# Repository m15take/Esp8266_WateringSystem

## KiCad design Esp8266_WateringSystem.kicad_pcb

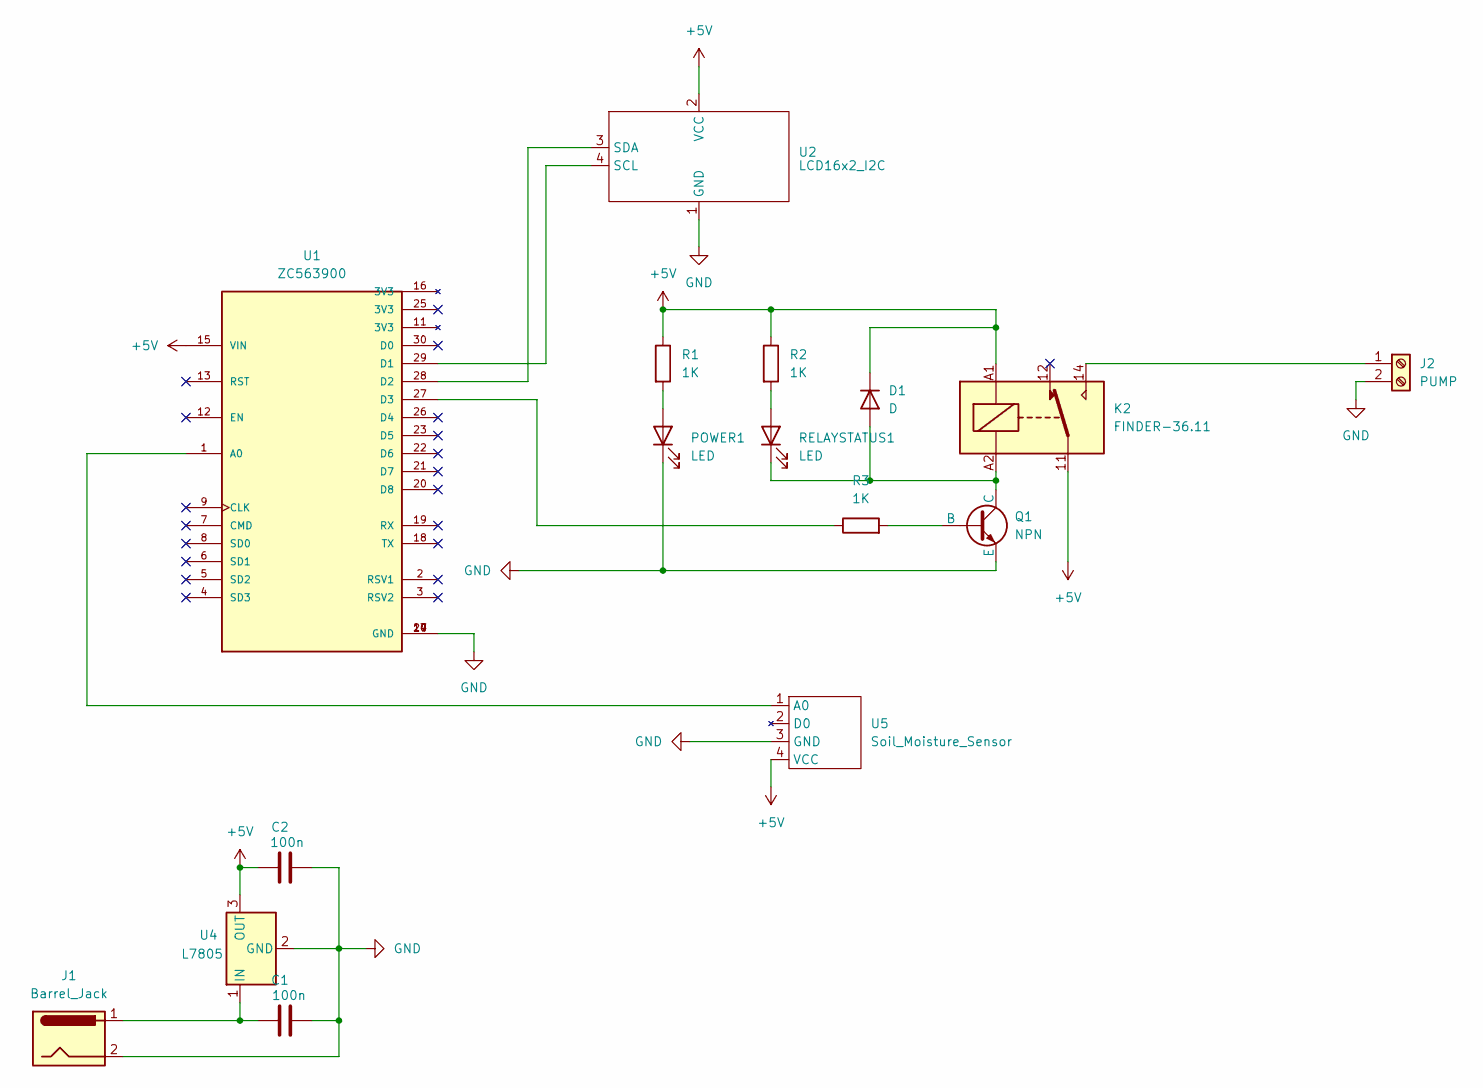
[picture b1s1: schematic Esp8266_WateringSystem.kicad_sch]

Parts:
C1, C2: 100n; CP_Radial_D4.0mm_P1.50mm
D1: D; D_A-405_P7.62mm_Horizontal
J1: Barrel_Jack; BarrelJack_Horizontal
J2: PUMP; TerminalBlock_Phoenix_MKDS-1,5-2-5.08_1x02_P5.08mm_Horizont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
K2: FINDER-36.11; Relay_SPDT_Finder_36.11
POWER1: LED; LED_D3.0mm
Q1: NPN; TO-92_Inline
R1, R2, R3: 1K; R_Axial_DIN0204_L3.6mm_D1.6mm_P5.08mm_Horizontal
RELAYSTATUS1: LED; LED_D3.0mm
U1: ZC563900; MODULE_ZC563900; PARTREV 1.0
U2: LCD16x2_I2C
U4: L7805; TO-220-3_Vertical
U5: Soil_Moisture_Sensor

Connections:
+5V: C2.1, D1.1 (K), K2.11, K2.A1, R1.1, R2.1, U1.15 (VIN), U2.2 (VCC), U4.3 (OUT), U5.4 (VCC)
GND: C1.2, C2.2, J1.2, J2.2, POWER1.1 (K), Q1.3 (E), U1.10 (GND), U1.14 (GND), U1.17 (GND), U1.24 (GND), U2.1 (GND), U4.2 (GND), U5.3 (GND)
unnamed: D1.2 (A), K2.A2, Q1.1 (C), RELAYSTATUS1.1 (K)
unnamed: J2.1, K2.14
unnamed: POWER1.2 (A), R1.2
unnamed: Q1.2 (B), R3.2
unnamed: R2.2, RELAYSTATUS1.2 (A)
unnamed: U1.1 (A0), U5.1 (A0)
unnamed: U1.29 (D1), U2.4 (SCL)
unnamed: U1.28 (D2), U2.3 (SDA)
unnamed: R3.1, U1.27 (D3)
unnamed: C1.1, J1.1, U4.1 (IN)

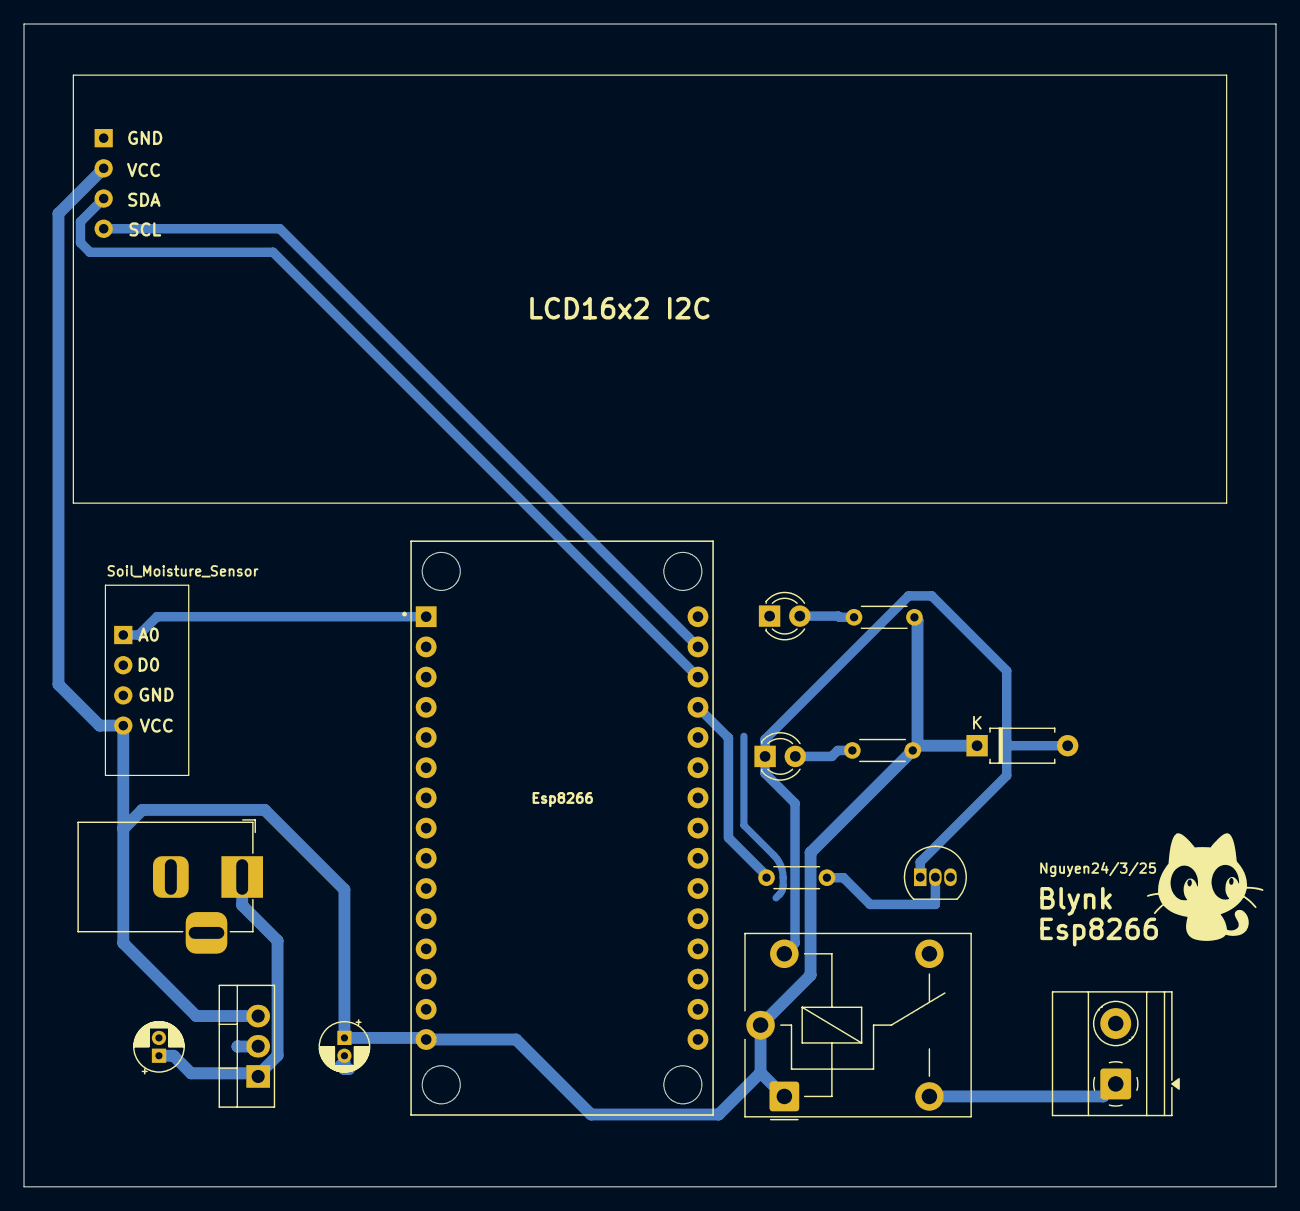
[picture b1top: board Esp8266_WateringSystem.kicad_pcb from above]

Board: 2 copper layers, 105.3 x 97.8 mm, 16 parts (0 on the bottom side), 12 nets.

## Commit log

2025-03-25 testgit
2025-03-25 test
2025-03-25 test2
2025-03-28 28_3_35
2025-04-14 o van ke
